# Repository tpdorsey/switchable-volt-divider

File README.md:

# Switchable Voltage Divider PCB — Circuit Overview and Build Guide

This PCB implements a **switchable resistive voltage divider** intended to derive accurate, repeatable fractions of a stable DC reference (nominally 10 V). Each divider tap produces a fixed ratio of the input voltage, selectable via a 1-pole, 5-position rotary switch. 

The design is optimized for trimming resistance values to achieve (relatively) precise divider values.

![Hand-assembled blue PCB voltage divider board with five selectable divider networks. The board shows multiple precision metal film resistors, blue Bourns 3362 trim potentiometers, and a single film capacitor, arranged around labeled divider sections. Three wires exit the right side for input, output, and ground. The layout is clean and symmetric, intended for a switchable precision voltage divider.](docs/front.png)

## Circuit Description

There are five taps on the PCB. Each tap on the PCB has space for two resistors and a trim pot (Bourns 3362).

Each tap is a **two-resistance voltage divider**:

```
Vin ── Rtop ──┬── Vout
              |
            Rbottom
              |
             GND
```

**Rtop** is a fixed value for all taps. (I used 100k.)

**Rbottom** is implemented as:

* A fixed resistor
* A small trim potentiometer (Bourns 3362)
* Optional second series resistor or jumper

This arrangement allows:

* Coarse ratio setting with fixed resistors
* Fine trimming with a low-value trimmer
* Good long-term stability by minimizing the trimmer’s contribution to total resistance

The rotary switch selects which divider output is routed to the output jack.

### Divider Equation

The fundamental voltage divider relationship is:

```
Vout = Vin * (Rbottom / (Rtop + Rbottom))
```

To design a divider for a desired ratio:

```
k = Vout / Vin
```

Solve for the shunt resistor:

```
Rbottom = (k / (1 - k)) * Rtop
```

### Example Divider Values 

Exact values matter. Let's say Rtop = 100,468 Ω.

| Divider ratio     | Vout (from 10V) | Rbottom (ideal) |
| ---- | --- | --- |
| 0.5               | 5.0 V          | 100,468 Ω          |
| 0.3               | 3.0 V          | 43,058 Ω        |
| 0.2               | 2.0 V          | 25,120 Ω        |
| 0.1               | 1.0 V          | 11,163 Ω        |
| 0.01              | 0.1 V          | 1,015 Ω         |

In practice, these are realized using nearby standard values plus the trim pot to dial in the exact ratio.

You can, of course, use whatever ratios you like.

## Build Notes

The PCB is designed around a 1-pole 5-position (using 1P/8-pos form factor) like the one available from pedal parts supplier [Love My Switches](https://lovemyswitches.com/mini-rotary-switch-1p5t-1-pole-5-position-knurled-shaft/) or [PedalPCB](https://www.pedalpcb.com/product/mini-rotary-switch-1p5t/).

The PCB is also designed to fit within a standard 125B aluminum enclosure with room to install your choice of inputs and outputs (banana jacks, RCA, etc.).

## Build Instructions (Summary)

1. **Populate fixed resistors first**

   * Use precision metal film resistors where possible.
   * Keep resistor types consistent across all taps to improve ratio tempco matching.

2. **Install the trimmer (Bourns 3362)**

   * Use the trimmer only for fine adjustment.
   * Aim to keep it near mid-range once trimmed.

3. **Install jumpers or series resistors**

   * If a second resistor footprint is unused, install a jumper.
   * Otherwise, use it to reduce the trim range and improve stability.

4. **Clean the PCB**

   * Thoroughly remove flux residue, especially around the 0.01 tap.
   * Leakage dominates errors at low-voltage, high-impedance nodes.

5. **Trim each divider**

   * Apply a stable input voltage.
   * Measure Vin and Vout with the same DMM.
   * Adjust the trimmer until the ratio (Vout / Vin) matches the target value.

6. **Final assembly**

   * Mount the PCB and switch in a metal enclosure.
   * Keep wiring short and thermally uniform.

### Notes on Use

* Divider accuracy should be evaluated **ratiometrically**, not as an absolute voltage.
* The 0.01 tap is most sensitive to leakage, temperature gradients, and contamination.
* A metal enclosure significantly improves short-term stability and repeatability.

This design is intentionally simple, adjustable, and reproducible.

## License

<a href="https://github.com/tpdorsey/switchable-volt-divider">Switchable Voltage Divider PCB</a> © 2026 by <a href="https://tpdorsey.com/">Terrence Dorsey</a> <p>is licensed under <a href="https://creativecommons.org/licenses/by-sa/4.0/">Creative Commons Attribution-ShareAlike 4.0 International</a><p>

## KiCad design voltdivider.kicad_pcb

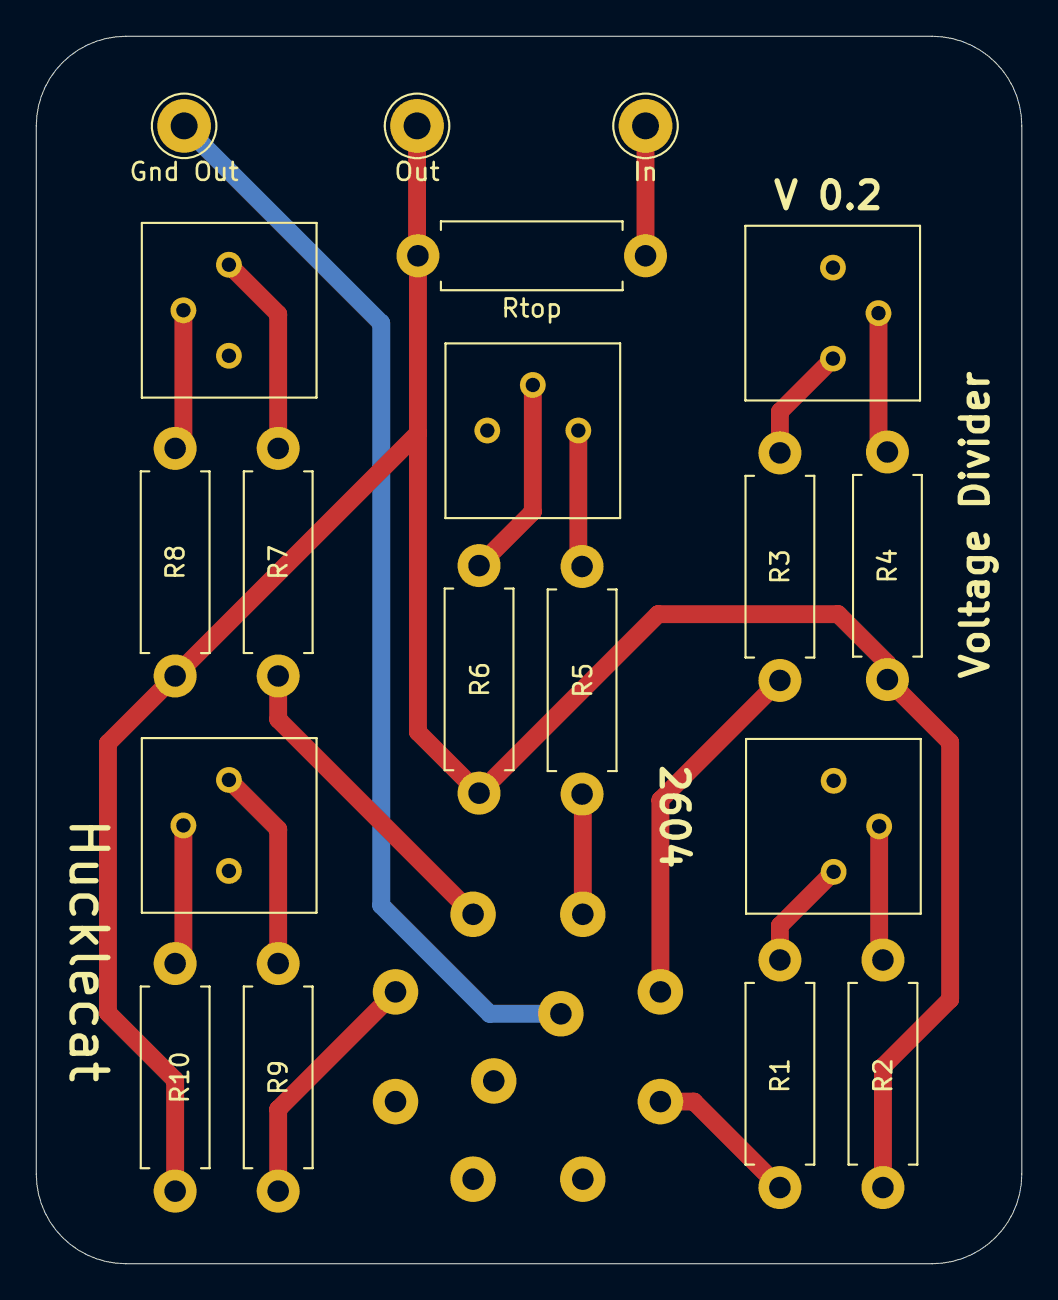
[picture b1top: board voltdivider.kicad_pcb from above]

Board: 2 copper layers, 55.0 x 68.5 mm, 20 parts (1 on the bottom side), 18 nets.

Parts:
Gnd Out: Conn_01x01_Pin; Pin_D1.3mm_L11.0mm_LooseFit
In: Conn_01x01_Pin; Pin_D1.3mm_L11.0mm_LooseFit
Out: Conn_01x01_Pin; Pin_D1.3mm_L11.0mm_LooseFit
R1, R2, R3, R4, R5, R6, R7, R8, R9, R10: R_US; R_Axial_DIN0411_L9.9mm_D3.6mm_P12.70mm_Horizontal
RV1, RV2, RV3, RV4, RV5: Trim; Potentiometer_Bourns_3386P_Vertical
Rtop: R Top; R_Axial_DIN0411_L9.9mm_D3.6mm_P12.70mm_Horizontal
SW1: SW_Rotary_1x8_MP; Rotary_Switch_8

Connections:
unnamed: Gnd Out.1, SW1.9
unnamed: In.1, Rtop.1
unnamed: Out.1, R2.2, R4.2, R6.2, R8.2, R10.2, Rtop.2
unnamed: R1.1, SW1.1
unnamed: R1.2, RV1.1
unnamed: R2.1, RV1.2
unnamed: R3.1, SW1.2
unnamed: R3.2, RV2.1
unnamed: R4.1, RV2.2
unnamed: R5.1, SW1.3
unnamed: R5.2, RV3.1
unnamed: R6.1, RV3.2
unnamed: R7.1, SW1.4
unnamed: R7.2, RV4.1
unnamed: R8.1, RV4.2
unnamed: R9.1, SW1.5
unnamed: R9.2, RV5.1
unnamed: R10.1, RV5.2

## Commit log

2026-02-08 creating documentation
2026-02-08 readme documentation and build images
2026-02-08 license
2026-02-08 ignore production files
2026-02-08 fix license
2026-02-09 readme fixes
